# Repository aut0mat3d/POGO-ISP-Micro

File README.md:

# POGO-ISP-Micro
Slightly modified to provide more space Tracks/Switch, added Pour keepout areas for easyer manual soldering.

# Note on PCB Ordering
On the bottom Layer there is a Pattern "JLCJLCJLCJLC" added which is a Placeholder for JLC Order#

PCB Diameter to choose: 1.2mm

POGO ISP Micro is small and reliable programming adapter for AVR ISP. It needs small ISP footprint on the PCB. Also it has RESET button, you can simply reset target device if you like.

# Why did you make it?
Standard ISP port is too big. It has 2.54mm pin pitch, so, it takes up a lot of space on the PCBs.

# What makes it special?
KiCAD library and footprint is ready to use [on Github!](https://github.com/hamityanik/POGO-ISP-Micro) Simply put it to your PCB design and you are ready to go with POGO ISP Micro. 

# POGO ISP Micro Specs.
- 1.27mm (0.05") pin pitch
- RESET Button
- Power led

# PCB Footprint Specs.
- 7.62mm (0.3") x 1.27 (0.05") total footprint area
- 2x 0.3mm guide holes on both sides, 4x pads

# KiCad Library & Footprint Preview

# How can I buy the original Design from hamityanik?
https://www.tindie.com/stores/iohippo/?ref=offsite_badges&utm_source=sellers_iohippo&utm_medium=badges&utm_campaign=badge_small

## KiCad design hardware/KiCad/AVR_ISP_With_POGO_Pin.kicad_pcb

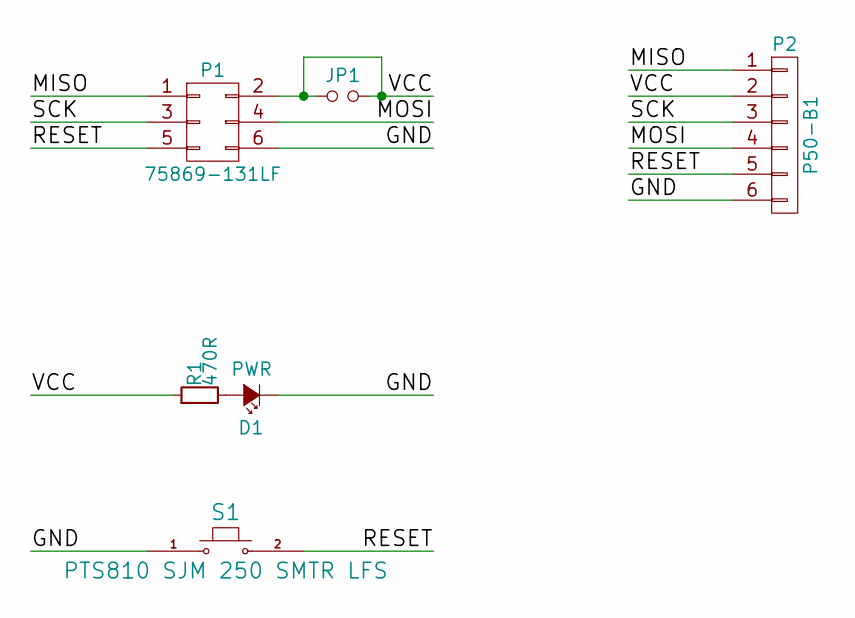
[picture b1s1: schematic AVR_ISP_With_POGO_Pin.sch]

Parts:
D1: PWR; LED_0805
JP1: Jumper_NO_Small; SJ_OPEN
P1: 75869-131LF; 2x6_idc_box_header_pcb_side_mount
P2: P50-B1; POGO_ISP
R1: 470R; R_0603
S1: PTS810 SJM 250 SMTR LFS; PTS810_tactile_push_button

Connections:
/GND: D1.1 (K), P1.6, P2.6, S1.1
/MISO: P1.1, P2.1
/MOSI: P1.4, P2.4
/RESET: P1.5, P2.5, S1.2
/SCK: P1.3, P2.3
/VCC: JP1.1, JP1.2, P1.2, P2.2, R1.1
unnamed: D1.2 (A), R1.2

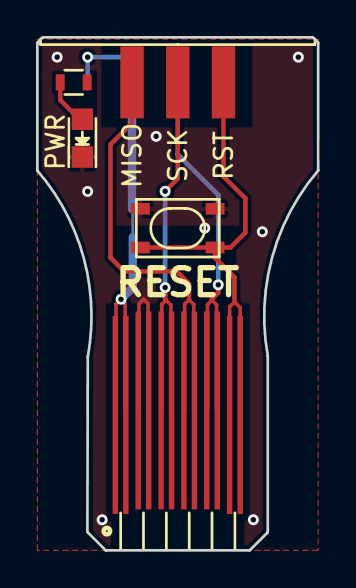
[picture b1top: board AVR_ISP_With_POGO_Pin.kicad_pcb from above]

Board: 2 copper layers, 15.6 x 28.5 mm, 6 parts (1 on the bottom side), 7 nets.

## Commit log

2020-06-10 Pour keepouts, spaces
    More Space to Pads of Switch, Pour keepouts added.
    All for making hand soldering more easy
2020-06-10 Added JLC Pattern for Order#
2020-06-10 Updates along newer Kicad version
2020-06-11 Fixed Error in Arc, panelized
2020-06-11 Gerber Output for single PCB
2020-06-11 Panelized with Mousebites
2020-06-11 Repanelized, reverted to V-Cut lines
    Mousebites dont do the job probably the rest also NOT
